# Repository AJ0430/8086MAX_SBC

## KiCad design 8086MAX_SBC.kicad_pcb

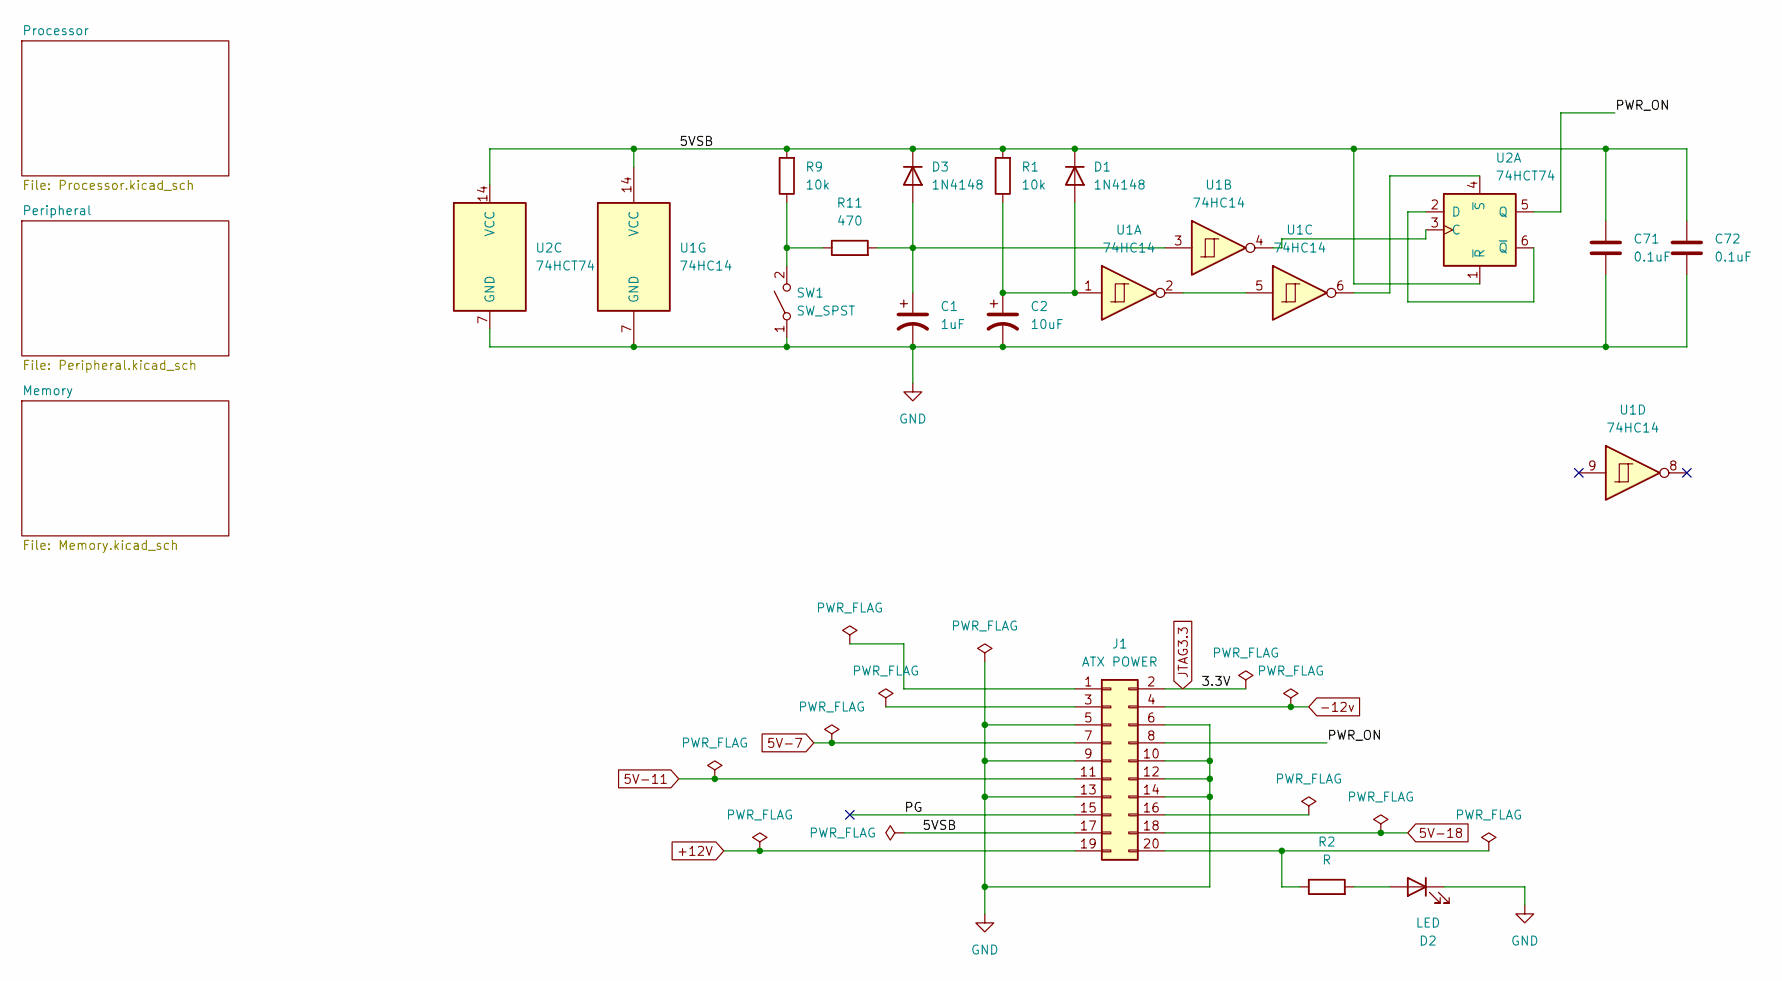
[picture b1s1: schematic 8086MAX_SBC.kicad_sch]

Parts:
C1: 1uF; CP_Radial_D6.3mm_P2.50mm
C2: 10uF; CP_Radial_D6.3mm_P2.50mm
C71, C72: 0.1uF; C_Disc_D8.0mm_W2.5mm_P5.00mm
D1, D3: 1N4148; D_DO-35_SOD27_P7.62mm_Horizontal
D2: LED; LED_D5.0mm
J1: ATX POWER; CONN_55660021-SD_20_MOL
R1, R9: 10k; R_Axial_DIN0207_L6.3mm_D2.5mm_P7.62mm_Horizontal
R2: R; R_Axial_DIN0207_L6.3mm_D2.5mm_P7.62mm_Horizontal
R11: 470; R_Axial_DIN0207_L6.3mm_D2.5mm_P7.62mm_Horizontal
SW1: SW_SPST; SW_Lever_1P2T_NKK_GW12LxH
U1: 74HC14; DIP-14_W7.62mm
U2: 74HCT74; DIP-14_W7.62mm

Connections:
5V-7: J1.7; also elsewhere on the board
5V-11: J1.11; also elsewhere on the board
5V-18: J1.18; also elsewhere on the board
+12V: J1.19; also elsewhere on the board
-12v: J1.4; also elsewhere on the board
/5VSB: C71.1, C72.1, D1.1 (K), D3.1 (K), J1.17, R1.2, R9.2, U1.14 (VCC), U2.1 (~R), U2.14 (VCC)
/PG: J1.15
/PWR_ON: J1.8, U2.5 (Q)
GND: C1.2, C2.2, C71.2, C72.2, D2.1 (K), J1.5, J1.6, J1.9, J1.10, J1.12, J1.13, J1.14, SW1.1 (A), U1.7 (GND), U2.7 (GND); also elsewhere on the board
JTAG3.3: J1.2; also elsewhere on the board
unnamed: C2.1, D1.2 (A), R1.1, U1.1
unnamed: D2.2 (A), R2.2
unnamed: C1.1, D3.2 (A), R11.2, U1.3
unnamed: J1.20, R2.1
unnamed: R9.1, R11.1, SW1.2 (B)
unnamed: U1.2, U1.5
unnamed: U1.4, U2.3 (C)
unnamed: U2.2 (D), U2.6 (~Q)
unnamed: U1.6, U2.4 (~S)

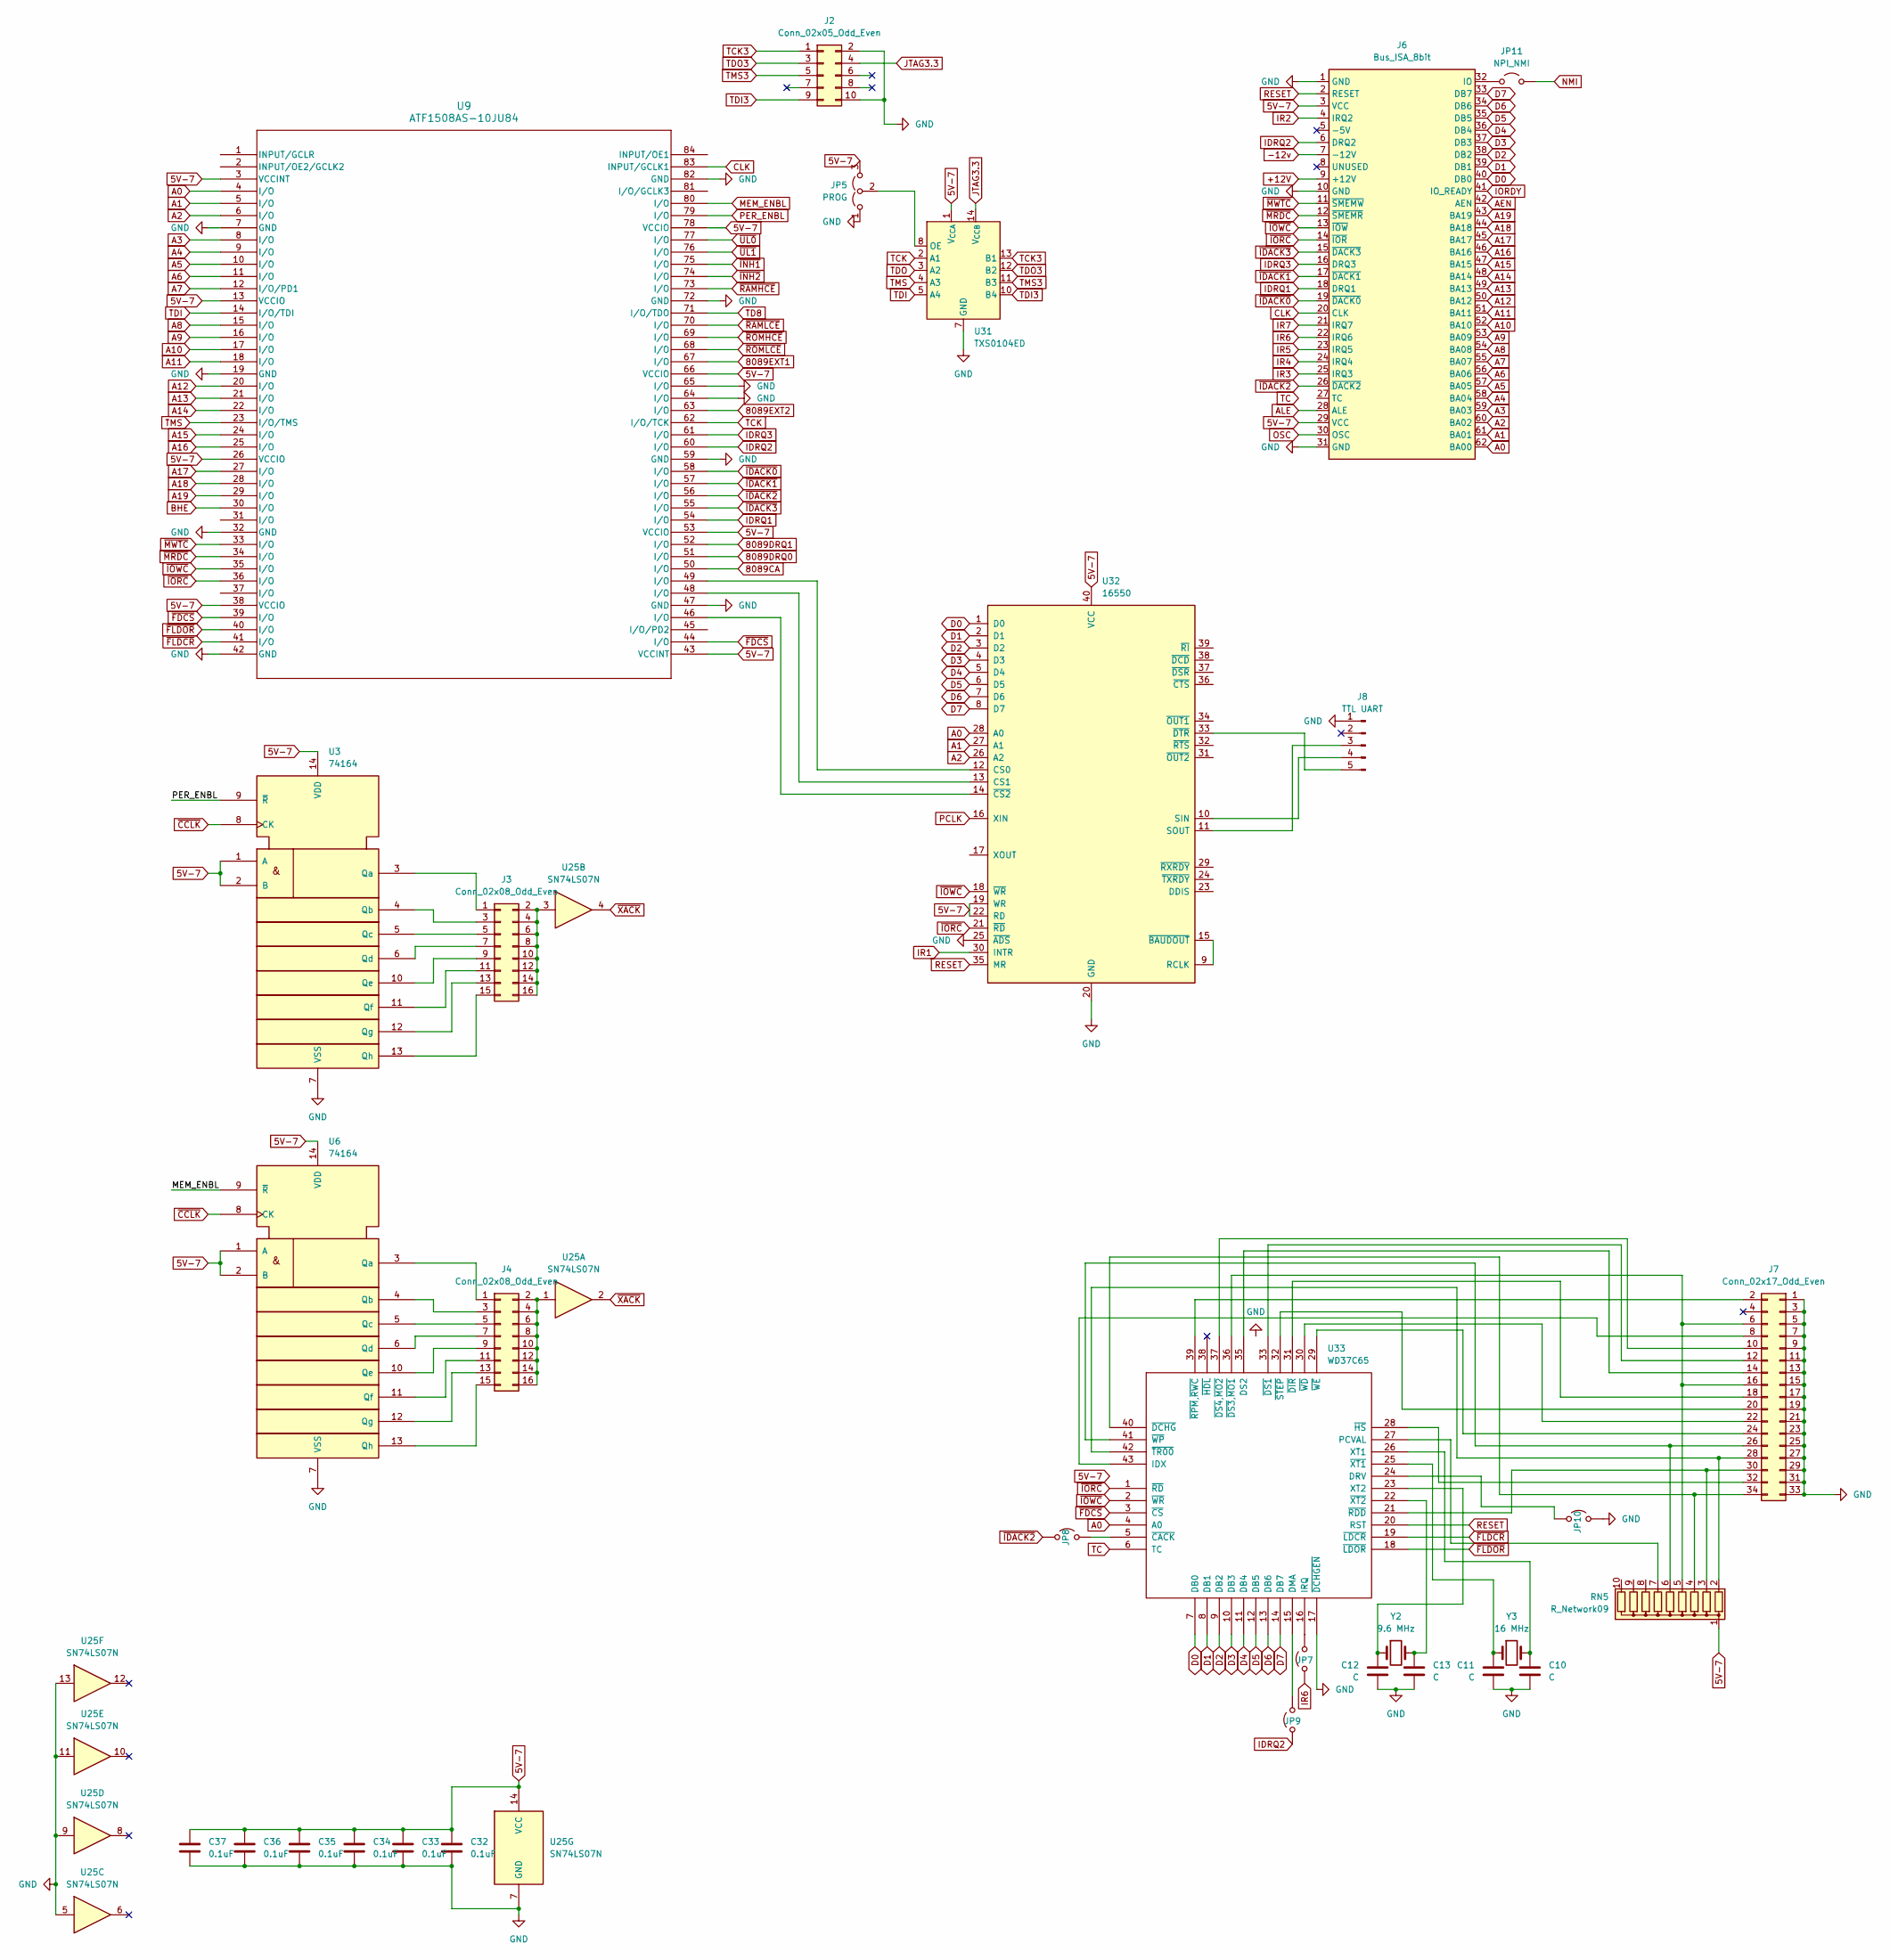
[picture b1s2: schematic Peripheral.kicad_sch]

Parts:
C10, C11, C12, C13: C; C_Disc_D8.0mm_W2.5mm_P5.00mm
C32, C33, C34, C35, C36, C37: 0.1uF; C_Disc_D8.0mm_W2.5mm_P5.00mm
J2: Conn_02x05_Odd_Even; PinHeader_2x05_P2.54mm_Vertical
J3, J4: Conn_02x08_Odd_Even; PinHeader_2x08_P2.54mm_Vertical
J6: Bus_ISA_8bit; TE_7-5530843-0
J7: Conn_02x17_Odd_Even; IDC-Header_2x17_P2.54mm_Latch_Vertical
J8: TTL UART; PinHeader_1x05_P2.54mm_Vertical
JP5: PROG; PinHeader_1x03_P2.54mm_Vertical
JP7, JP8, JP9, JP10: Jumper_2_Open; PinHeader_1x02_P2.54mm_Vertical
JP11: NPI_NMI; PinHeader_1x02_P2.54mm_Vertical
RN5: R_Network09; R_Array_SIP10
U3, U6: 74164; DIP-14_W7.62mm
U9: ATF1508AS-10JU84; PLCC-84_THT-Socket
U25: SN74LS07N; DIP-14_W7.62mm
U31: TXS0104ED; SOIC-14_3.9x8.7mm_P1.27mm
U32: 16550; DIP-40_W15.24mm
U33: WD37C65; PLCC-44_THT-Socket
Y2: 9.6 MHz; Crystal_HC49-U_Vertical
Y3: 16 MHz; Crystal_HC49-U_Vertical

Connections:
5V-7: C32.1, C33.1, C34.1, C35.1, C36.1, C37.1, J6.3 (VCC), J6.29 (VCC), JP5.3 (B), RN5.1 (common), U3.1 (A), U3.2 (B), U3.14 (VDD), U6.1 (A), U6.2 (B), U6.14 (VDD), U9.3 (VCCINT), U9.13 (VCCIO), U9.26 (VCCIO), U9.38 (VCCIO), U9.43 (VCCINT), U9.53 (VCCIO), U9.66 (VCCIO), U9.78 (VCCIO), U25.14 (VCC), U31.1 (V_{CCA}), U32.19 (WR), U32.22 (RD), U32.40 (VCC), U33.44 (VCC); also elsewhere on the board
8089CA: U9.50 (I/O); also elsewhere on the board
8089DRQ0: U9.51 (I/O); also elsewhere on the board
8089DRQ1: U9.52 (I/O); also elsewhere on the board
8089EXT1: U9.67 (I/O); also elsewhere on the board
8089EXT2: U9.63 (I/O); also elsewhere on the board
+12V: J6.9 (+12V); also elsewhere on the board
-12v: J6.7 (-12V); also elsewhere on the board
A0: J6.62 (BA00), U9.4 (I/O), U32.28 (A0), U33.4 (A0); also elsewhere on the board
A1: J6.61 (BA01), U9.5 (I/O), U32.27 (A1); also elsewhere on the board
A2: J6.60 (BA02), U9.6 (I/O), U32.26 (A2); also elsewhere on the board
A3: J6.59 (BA03), U9.8 (I/O); also elsewhere on the board
A4: J6.58 (BA04), U9.9 (I/O); also elsewhere on the board
A5: J6.57 (BA05), U9.10 (I/O); also elsewhere on the board
A6: J6.56 (BA06), U9.11 (I/O); also elsewhere on the board
A7: J6.55 (BA07), U9.12 (I/O/PD1); also elsewhere on the board
A8: J6.54 (BA08), U9.15 (I/O); also elsewhere on the board
A9: J6.53 (BA09), U9.16 (I/O); also elsewhere on the board
A10: J6.52 (BA10), U9.17 (I/O); also elsewhere on the board
A11: J6.51 (BA11), U9.18 (I/O); also elsewhere on the board
A12: J6.50 (BA12), U9.20 (I/O); also elsewhere on the board
A13: J6.49 (BA13), U9.21 (I/O); also elsewhere on the board
A14: J6.48 (BA14), U9.22 (I/O); also elsewhere on the board
A15: J6.47 (BA15), U9.24 (I/O); also elsewhere on the board
A16: J6.46 (BA16), U9.25 (I/O); also elsewhere on the board
A17: J6.45 (BA17), U9.27 (I/O); also elsewhere on the board
A18: J6.44 (BA18), U9.28 (I/O); also elsewhere on the board
A19: J6.43 (BA19), U9.29 (I/O); also elsewhere on the board
AEN: J6.42 (AEN); also elsewhere on the board
ALE: J6.28 (ALE); also elsewhere on the board
BHE: U9.30 (I/O); also elsewhere on the board
CLK: J6.20 (CLK), U9.83 (INPUT/GCLK1); also elsewhere on the board
D0: J6.40 (DB0), U32.1 (D0), U33.7 (DB0); also elsewhere on the board
D1: J6.39 (DB1), U32.2 (D1), U33.8 (DB1); also elsewhere on the board
D2: J6.38 (DB2), U32.3 (D2), U33.9 (DB2); also elsewhere on the board
D3: J6.37 (DB3), U32.4 (D3), U33.10 (DB3); also elsewhere on the board
D4: J6.36 (DB4), U32.5 (D4), U33.11 (DB4); also elsewhere on the board
D5: J6.35 (DB5), U32.6 (D5), U33.12 (DB5); also elsewhere on the board
D6: J6.34 (DB6), U32.7 (D6), U33.13 (DB6); also elsewhere on the board
D7: J6.33 (DB7), U32.8 (D7), U33.14 (DB7); also elsewhere on the board
GND: C10.2, C11.2, C12.2, C13.2, C32.2, C33.2, C34.2, C35.2, C36.2, C37.2, J2.2, J2.10, J6.1 (GND), J6.10 (GND), J6.31 (GND), J7.1, J7.3, J7.5, J7.7, J7.9, J7.11, J7.13, J7.15, J7.17, J7.19, J7.21, J7.23, J7.25, J7.27, J7.29, J7.31, J7.33, J8.1, JP5.1 (A), JP10.2 (B), U3.7 (VSS), U6.7 (VSS), U9.7 (GND), U9.19 (GND), U9.32 (GND), U9.42 (GND), U9.47 (GND), U9.59 (GND), U9.64 (I/O), U9.65 (I/O), U9.72 (GND), U9.82 (GND), U25.5, U25.7 (GND), U25.9, U25.11, U25.13, U31.7 (GND), U32.20 (GND), U32.25 (~ADS), U33.17 (~DCHGEN), U33.34 (VSS); also elsewhere on the board
IDRQ1: J6.18 (DRQ1), U9.54 (I/O)
IDRQ2: J6.6 (DRQ2), JP9.1 (A), U9.60 (I/O)
IDRQ3: J6.16 (DRQ3), U9.61 (I/O)
IORDY: J6.41 (IO_READY); also elsewhere on the board
IR1: U32.30 (INTR); also elsewhere on the board
IR2: J6.4 (IRQ2)
IR3: J6.25 (IRQ3); also elsewhere on the board
IR4: J6.24 (IRQ4); also elsewhere on the board
IR5: J6.23 (IRQ5); also elsewhere on the board
IR6: J6.22 (IRQ6), JP7.1 (A); also elsewhere on the board
IR7: J6.21 (IRQ7); also elsewhere on the board
JTAG3.3: J2.4, U31.14 (V_{CCB}); also elsewhere on the board
MEM_ENBL: U6.9 (~R), U9.80 (I/O)
NMI: JP11.2 (B); also elsewhere on the board
unnamed: J3.1, U3.3 (Qa)
unnamed: J3.3, U3.4 (Qb)
unnamed: J3.5, U3.5 (Qc)
unnamed: J3.7, U3.6 (Qd)
unnamed: J3.9, U3.10 (Qe)
unnamed: J3.2, J3.4, J3.6, J3.8, J3.10, J3.12, J3.14, J3.16, U25.3
unnamed: J3.11, U3.11 (Qf)
unnamed: J3.13, U3.12 (Qg)
unnamed: J3.15, U3.13 (Qh)
unnamed: J4.1, U6.3 (Qa)
unnamed: J4.3, U6.4 (Qb)
unnamed: J4.5, U6.5 (Qc)
unnamed: J4.7, U6.6 (Qd)
unnamed: J4.9, U6.10 (Qe)
unnamed: J4.2, J4.4, J4.6, J4.8, J4.10, J4.12, J4.14, J4.16, U25.1
unnamed: J4.11, U6.11 (Qf)
unnamed: J4.13, U6.12 (Qg)
unnamed: J4.15, U6.13 (Qh)
unnamed: J6.32 (IO), JP11.1 (A)
unnamed: J7.2, U33.39 (~RPM,~RWC)
unnamed: J7.8, U33.43 (IDX)
unnamed: J7.10, U33.37 (~DS4,~MO2)
unnamed: J7.12, U33.33 (~DS1)
unnamed: J7.14, U33.35 (DS2)
unnamed: J7.6, J7.16, RN5.5 (R4), U33.36 (~DS3,~MO1)
unnamed: J7.18, U33.31 (~DIR)
unnamed: J7.20, U33.32 (~STEP)
unnamed: J7.22, U33.30 (~WD)
unnamed: J7.24, U33.29 (~WE)
unnamed: J7.26, RN5.6 (R5), U33.41 (~WP)
unnamed: J7.28, RN5.2 (R1), U33.42 (~TR00)
unnamed: J7.30, RN5.3 (R2), U33.21 (~RDD)
unnamed: J7.32, U33.28 (~HS)
unnamed: J7.34, RN5.4 (R3), U33.40 (~DCHG)
unnamed: J8.3, U32.11 (SOUT)
unnamed: J8.4, U32.10 (SIN)
unnamed: J8.5, U32.33 (~DTR)
unnamed: JP5.2 (C), U31.8 (OE)
unnamed: JP7.2 (B), U33.16 (IRQ)
unnamed: JP8.2 (B), U33.5 (~CACK)
unnamed: JP9.2 (B), U33.15 (DMA)
unnamed: JP10.1 (A), U33.24 (DRV)
unnamed: RN5.7 (R6), U33.27 (PCVAL)
unnamed: U9.49 (I/O), U32.12 (CS0)
unnamed: U9.48 (I/O), U32.13 (CS1)
unnamed: U32.9 (RCLK), U32.15 (~BAUDOUT)
unnamed: U9.46 (I/O), U32.14 (~CS2)
unnamed: C10.1, U33.26 (XT1), Y3.2
unnamed: C12.1, U33.23 (XT2), Y2.1
unnamed: C11.1, U33.25 (~XT1), Y3.1
unnamed: C13.1, U33.22 (~XT2), Y2.2
OSC: J6.30 (OSC); also elsewhere on the board
PCLK: U32.16 (XIN); also elsewhere on the board
PER_ENBL: U3.9 (~R), U9.79 (I/O)
RESET: J6.2 (RESET), U32.35 (MR), U33.20 (RST); also elsewhere on the board
TC: U33.6 (TC); also elsewhere on the board
TCK: U9.62 (I/O/TCK), U31.2 (A1)
TCK3: J2.1, U31.13 (B1)
TD8: U9.71 (I/O/TDO)
TDI: U9.14 (I/O/TDI), U31.5 (A4)
TDI3: J2.9, U31.10 (B4)
TDO: U31.3 (A2)
TDO3: J2.3, U31.12 (B2)
TMS: U9.23 (I/O/TMS), U31.4 (A3)
TMS3: J2.5, U31.11 (B3)
~CCLK: U3.8 (CK), U6.8 (CK); also elsewhere on the board
~FDCS: U9.39 (I/O), U9.44 (I/O), U33.3 (~CS)
~FLDCR: U9.41 (I/O), U33.19 (~LDCR)
~FLDOR: U9.40 (I/O), U33.18 (~LDOR)
~IDACK0: J6.19 (~DACK0), U9.58 (I/O)
~IDACK1: J6.17 (~DACK1), U9.57 (I/O)
~IDACK2: J6.26 (~DACK2), JP8.1 (A), U9.56 (I/O)
~IDACK3: J6.15 (~DACK3), U9.55 (I/O)
~INH1: U9.75 (I/O); also elsewhere on the board
~INH2: U9.74 (I/O); also elsewhere on the board
~IORC: J6.14 (~IOR), U9.36 (I/O), U32.21 (~RD), U33.1 (~RD); also elsewhere on the board
~IOWC: J6.13 (~IOW), U9.35 (I/O), U32.18 (~WR), U33.2 (~WR); also elsewhere on the board
~MRDC: J6.12 (~SMEMR), U9.34 (I/O); also elsewhere on the board
~MWTC: J6.11 (~SMEMW), U9.33 (I/O); also elsewhere on the board
~RAMHCE: U9.73 (I/O); also elsewhere on the board
~RAMLCE: U9.70 (I/O); also elsewhere on the board
~ROMHCE: U9.69 (I/O); also elsewhere on the board
~ROMLCE: U9.68 (I/O); also elsewhere on the board
~UL0: U9.77 (I/O); also elsewhere on the board
~UL1: U9.76 (I/O); also elsewhere on the board
~XACK: U25.2, U25.4; also elsewhere on the board
